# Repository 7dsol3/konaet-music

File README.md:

# KONAET Music

**A connected workspace. Music, public research, voice and a checkout code of your own.**

[Open KONAET Music on GitHub Pages](https://7dsol3.github.io/konaet-music/) ·
[Open the Sound Lab](https://7dsol3.github.io/konaet-music/sound-lab/) ·
[Audio methods](docs/SOUND-LAB.md) · [Digital hardware](docs/AUDIO-HARDWARE.md)

The GitHub Pages edition runs the catalog, comparison, bag, local music assistant,
checkout quotes, three QR artworks, test credits, logic lab and Sound Lab in the
visitor's browser. It does not depend on the author's PC or a temporary tunnel.
QR links carry a compact item selection and expiry; another device recomputes
the amount from the same bundled catalog. Quotes and receipts in this edition
are **unsigned browser demonstrations**, not bank requests or server-sealed records.
Public research calls selected external APIs and depends on network access.
No private customer/order fixtures or neural model keys are bundled.

Download the source and double-click **Run Browser Demo.cmd** on Windows, or run
`python scripts/serve_browser.py` on any supported PC. Python 3.11+ is required;
this browser launcher needs no pip packages. See [browser delivery](docs/GITHUB-PAGES.md).
The full Python edition remains available for server sessions, private fixture
order verification, sealed sandbox receipts and an optional local model.

This is the **separate product evolution** of the submitted
[Empório da Música technical case](https://github.com/7dsol3/emporio-musica-ai-agent).
The original submission is preserved at revision
`aefc6f54191eb00c52d7a9f8df85c1c3a201c5b6`. Its history is retained here;
new work belongs to this repository. [Scope and decisions](docs/EVOLUTION.md).

The customer interface and replies are in **English**. Catalog prices remain
in **BRL**. The store, inventory and customer fixtures are fictional supplied
case data. No real purchase, stock reservation, refund or charge is executed.

## Explore the product

**[Explore the H-01A KiCad project](hardware/h01-audio/README.md)** — editable
schematic, routed PCB, STEP/GLB, BOM and review Gerbers. Zero ERC/DRC/parity
violations; external FPGA required, physical bring-up not performed.

*Exported integer reference trace. Live analysis is in the Sound Lab; this animation
is not physical-device telemetry.*

- Browse 65 recorded instruments by category, brand, model, availability and budget.
- Compare two or three instruments using recorded specifications.
- Open a product, add it to a session bag and change quantities.
- Prepare a server-calculated, fifteen-minute checkout preview with a unique KONAET Code.
- Download the original vector code or open the quote on another device when deployed on HTTPS.
- Ask KONAET about instruments, prices, installments, store policies and a verified fixture order.
- Use the native Portuguese or English interface; voice drafts and spoken replies follow that language and remain opt-in.
- Install the responsive PWA on supported devices. Every command also works by typing.
- Choose Prisma or original liquid glass, with color, transparency, blur, corners, refractive light and comfort controls. The look is shared with Sound Lab and can be exported or imported.
- Research public knowledge, scholarly metadata and code with dated source links.
- Switch the voice/text assistant between the music desk and explicit research scopes.
- Inspect actual connection states and export source briefs from the current tab.
- Try a private test wallet, approve/decline a sandbox transaction and verify its sealed receipt.
- Export a private opening compatible with the Sovereign receipt SDK, without submitting to a network.
- Explore a Python/SystemVerilog credit gate and its logical trace in the hardware lab.
- Play named notes, build triads, use a metronome and export a project-authored four-chord study.
- Tune a sustained note with explicit microphone permission; analyze a local audio file without uploading it.
- Ask checked music rules to explain a pitch/triad estimate, with an optional, clearly named model suggestion.
- Generate phase controls for the H-01 digital audio core, hear its reference voice and inspect exact PCM metrics.

The **2.2 Sound Lab** is a separate, lazy page at `/sound-lab`. Its browser DSP is
project code, not a trained song-recognition model. H-01 includes synthesizable
SystemVerilog for three phase voices, exact level/energy meters and I²S transmit
and receive paths. The live site executes the reference model; no physical FPGA,
microphone board or DAC is connected to the server.

[Methods and limits](docs/SOUND-LAB.md) · [Hardware interfaces and equations](docs/AUDIO-HARDWARE.md) ·
[Production gates](docs/PRODUCTION-GATES.md) · [External-runtime comparison protocol](docs/RUNTIME-COMPARISON.md)

The listening room keeps its floating shell, tool rail, catalog search and
separate Discover, Research and Guide areas. Prisma supplies graphite materials,
physical controls and selected refractive edges; the original green glass room
remains selectable. Sound Lab shares the settings and typography. The supplied
six-board reference is mapped to actual functions in [Prisma Studio](docs/PRISMA-STUDIO.md).
The native PT/EN interface avoids browser translation altering the layout or
instrument identifiers. The browser assistant handles Portuguese instrument
families, Brazilian budget amounts and exact model lookups.

The room artwork is an original WebP of about 18 KB. Fonts are bundled under
their [Open Font Licenses](docs/FONT-PROVENANCE.md); there are no external font
requests or animation frameworks. Main text assets have a 280 KB raw / 86 KB
gzip budget, with separate 30 KB bitmap and 100 KB font budgets. Sound Lab's
audio engine stays lazy. Browser reviews cover PT/EN at seven widths, alongside
DOM and audio lifecycle tests. [Art direction and checks](docs/LISTENING-ROOM.md).

## Run locally

Python 3.11 or 3.12 is recommended. No paid key is required for the local mode.

```powershell
py -3.12 -m venv .venv
.\.venv\Scripts\python.exe -m pip install -r requirements-runtime.lock
.\.venv\Scripts\python.exe -m pip install --no-deps --no-build-isolation -e .
.\.venv\Scripts\python.exe -m emporio serve
```

Open **http://127.0.0.1:8000**. Alternatively, double-click **Run Offline.cmd**.
For the standalone browser edition instead, use **Run Browser Demo.cmd**; it
starts at **http://127.0.0.1:8040** and keeps working while that window is open.
The default agent uses explicit local rules and the same authoritative tools.
It is a deterministic router, not a neural language model.

For an actual local neural planner on Windows x64:

```powershell
.\.venv\Scripts\python.exe scripts/local_model.py setup
.\.venv\Scripts\python.exe scripts/local_model.py app
```

Or double-click **Run Demo.cmd**. Setup verifies approximately 665 MB of official
Qwen3-0.6B Q8_0 and llama.cpp assets before loading them. Qwen is an **external
inference model**, not weights trained by KONAET. Engine files are compared
against the pinned archive before execution. [Provenance](docs/PROVENANCE.md).

The terminal commands remain available:

```text
python -m emporio chat --language en
python -m emporio verify-audit
```

## KONAET Code

The illustration above is an actual scannable **source-link demonstration**.
It opens this repository. It is not a payment request or an active checkout.

Real application codes identify individual checkout previews. The backend
creates a cryptographically random reference, recalculates current prices,
checks quantities, applies eligible PIX pricing without stacking promotions,
and binds the result to an expiring immutable quote. Retrying the same request
for an unchanged bag returns the same quote. Changed contents require a new request.

The QR encoder is **Segno**, with high error correction and a four-module quiet
zone. KONAET's vector composition, brand, colors, framing and checkout binding
are implemented in [konaet_code.py](emporio/konaet_code.py). Branding does not
cover the finder patterns or data. No third-party QR image service receives
the checkout URL. An independent ZXing decoder tests the actual rendered SVG
at two widths and three orientations.

Choose **Signature**, **Orbit** or **Studio** artwork. Each keeps the exact same
quote URL and unobstructed symbol. The drawings sit outside the quiet zone.
The data itself has three source-generated treatments: horizontal circuit traces,
connected constellation dots and vertical studio ribbons. Finder, alignment,
timing, format and version modules retain their exact square geometry. No custom
scanner is required; compatibility is checked with an independent QR decoder.
The server uses a versioned unit-rounding rule consistently in bag and quote;
fractional-cent regression tests and every available catalog product are checked.

| Orbit / science | Studio / guitar |
| --- | --- |
|  |  |

These two documentation codes open the GitHub entrance. Active checkout codes
are generated separately for their unique expiring quote.

The link is a capability: anyone holding it can view its **public product
quote** until expiry. No email, customer ID, chat or session cookie is encoded.
Shipping is excluded. Stock is not reserved. The QR itself never proves payment.

For real commerce, the merchant needs an authorized store backend and payment
account. The researched next integration is a provider-issued Pix request with
idempotency and verified server-side confirmation. It is **not implemented or
enabled by a payment key in this release**. [Payment boundary and research](docs/PAYMENTS.md).

KONAET's new [sandbox checkout](docs/CHECKOUT-SANDBOX.md) is implemented separately:
test credits, typed intent creation, an atomic terminal outcome, exactly-once
debit on retries/concurrent confirmation, and server-sealed receipts. It does
not create a Pix payment, reserve stock or replace a regulated payment network.

## Voice and commands

Press the microphone in the assistant to request browser speech recognition.
Nothing listens on page load. The English transcript becomes an editable draft;
you choose when to send it. Enable **Read replies aloud** to use available
browser speech synthesis. Closing the assistant stops capture and playback.

Try:

```text
Show acoustic guitars under BRL 1,000
Tell me about the first one
Can I pay for it in 12 installments?
Compare the first two
Add the first one to my bag
Show my bag
Prepare checkout
```

The last commands are explicit UI actions over already displayed product IDs.
They cannot charge a card, submit a bank transfer or authorize a refund.

SpeechRecognition support varies. Some browsers send audio to their own speech
service; this is **not guaranteed offline speech**. Unsupported or denied
microphones keep typed chat available. Real microphone, mobile-device and
speech-quality testing is still required. [Voice contract](docs/VOICE.md).

## How the agent works

```mermaid
flowchart LR
  C[English text or reviewed voice draft] --> P[Local router or optional model planner]
  P --> G[Intent constraints and typed tool guards]
  G --> T[Catalog / policies / payment math / scoped order]
  T --> R[Grounded answer and source receipts]
  U[Explicit customer action] --> B[Session bag]
  B --> Q[Repriced expiring quote]
  Q --> K[KONAET Code]
```

Prices and policy outcomes come from checked tool results. Explicit category,
budget, product and transaction arguments cannot be widened by the model.
Order tools use session ownership in SQL. Private order requests bypass model
planning; provider context contains only allowlisted public product fields,
and order references are redacted from user history.

The local audit chain detects modification of existing receipts. It has no
external anchor and does not prevent an operator from replacing the entire
log. This product does not claim a Sovereign-finalized receipt or independent audit.

The inherited policy module remains version-pinned to the supplied PDF. Return
messages with missing packaging/materials now go to review rather than being
treated as fully satisfied. Ambiguous claims remain preliminary guidance.

## Configuration

| Variable | Purpose |
| --- | --- |
| `EMPORIO_PROVIDER` | `local` or `openai_compatible`; local is the default |
| `EMPORIO_MODEL_URL` | Native function-calling endpoint; HTTPS or HTTP loopback |
| `EMPORIO_MODEL` | Model ID accepted by your endpoint |
| `EMPORIO_MODEL_KEY` | Optional provider key, backend environment only |
| `EMPORIO_MODEL_TIMEOUT` | Planning timeout, 1–60 seconds |
| `EMPORIO_DATA_DIR` | Optional authorized replacement for the six original CSVs and manual |
| `EMPORIO_STATE_DIR` | Writable private state directory; defaults to the user's local state folder |
| `KONAET_PUBLIC_URL` | Trusted HTTPS origin used for checkout links; loopback is allowed for local use |
| `KONAET_MODEL_CACHE` | Optional directory holding verified neural-model assets |
| `KONAET_BRAVE_SEARCH_KEY` | Optional backend-only key for the general Web index; other documented public indexes work without it |
| `KONAET_GATEWAY_SECRET` | Preview-origin authentication, supplied only at runtime to the gateway and Python origin |

Variables are read from the process environment. `.env.example` is documentation,
not a file loader. A packaged wheel includes the case data and the web assets;
installation outside this checkout is tested.

## Host the Python application

The frontend and API must share an origin. Static GitHub Pages cannot execute
this Python/SQLite backend. A repository URL is not a hosted service.

An optional [Render demo blueprint](render.yaml) is included. It needs a Render
account, a connected copy of this repository and `KONAET_PUBLIC_URL` set to the
assigned HTTPS origin. It is not deployed automatically by cloning the code.
The free demo filesystem is ephemeral: sessions and quotes can disappear on
restart. Do not use it as a real merchant's order database.

For a Python host with an HTTPS reverse proxy:

```text
pip install -r requirements-runtime.lock
pip install --no-deps --no-build-isolation .
KONAET_PUBLIC_URL=https://your-demo.example PORT=8000 python scripts/serve.py
```

Set environment variables with your shell's syntax. The deployment entrypoint
requires the HTTPS origin, binds the assigned port and uses one process. A
production multi-instance service needs shared storage, verified customer
identity, independent rate limits, secrets management and monitoring.

## Verification

```text
python -m pip install -r requirements.lock
python -m pip install --no-deps --no-build-isolation -e .
python -m pytest
python scripts/verify_frontend.py
python scripts/verify_wheel.py
python scripts/capture_product_evidence.py
```

Interface event-contract tests run with Node 24.22.2:

```text
cd tests/ui
npm ci --ignore-scripts
cd ../..
node --test tests/ui/interface.test.mjs
```

These execute DOM events with API doubles. They do not render pixels or prove
physical microphone behavior. The native/browser-control bridge was unavailable
during implementation, so a new browser visual review is still outstanding.

See [2.1 validation and exact evidence](docs/VALIDATION-2.1.md) for the measured scope,
fresh model conversations, package tests and known limits. Historical screenshots
and `docs/ui-check.json` came from the original case and do not depict this redesign.

## Licensing and next work

Project-authored contributions use MIT. The frozen retrieval module retains
the Konaet Research and Commercial License, and the supplied case fixtures
retain their separate terms. The MIT license does not relicense those materials.
[Full notices](THIRD_PARTY_NOTICES.md). Qwen, llama.cpp, Segno and other dependencies
remain attributed to their authors.

OpenAI Codex assisted implementation, research, tests and documentation. The
project records observed failures and uses deterministic guardrails around
optional model planning. No claim of consciousness, general superiority,
original QR encoding, or outperforming Siri/Alexa is made.

Next: real browser/device accessibility and voice trials; authorized live-store
adapters; a payment-provider sandbox; broader unseen paraphrase evaluation;
measured concurrent-load testing and a production identity/storage architecture.

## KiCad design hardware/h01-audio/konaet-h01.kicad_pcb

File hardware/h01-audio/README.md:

# KONAET H-01A — audio carrier

An editable **KiCad 10.0.8** project for the H-01 digital audio core. This revision
connects an **external FPGA** to a stereo line DAC and an external I²S microphone
module. It supplies the 12.288 MHz reference clock and the carrier's 3.3 V rail.
It does not contain an FPGA, inference processor, Wi-Fi radio or trained AI model.

**Review prototype.** ERC, DRC, schematic/PCB parity and all 105 connected pad
assignments pass. There are no waived DRC violations or disconnected nets.
Those results verify the design files; the board has not been fabricated,
powered, acoustically measured or approved for manufacture. See
[validation.json](validation.json) for source hashes and [bring-up](BRING-UP.md).

## Open and inspect

1. Open [konaet-h01.kicad_pro](konaet-h01.kicad_pro) with KiCad 10.0.8 or newer.
2. Open PCB Editor and press **Alt+3** for KiCad's interactive 3D Viewer.
3. Rotate, zoom, inspect both sides and toggle component visibility.
4. Open the Schematic Editor to inspect the named nets and manufacturer pins.

The project includes its footprint library and STEP models with relative paths.
It does not need a global library installation to view this design.
Y1 deliberately uses a **3225 crystal-shaped geometric proxy**; its appearance
is not an Abracon-certified mechanical model. All other models are the frozen
KiCad library models listed in [LIBRARIES.md](LIBRARIES.md).

| Deliverable | File |
| --- | --- |
| Schematic, editable / PDF | [KiCad schematic](konaet-h01.kicad_sch) · [PDF](schematic.pdf) |
| Routed PCB, editable / layer PDF | [PCB](konaet-h01.kicad_pcb) · [PDF](layout.pdf) |
| CAD assembly | [STEP](konaet-h01.step) · [GLB](konaet-h01.glb) |
| Rendered views | [Top](board-top.png) · [Bottom](board-bottom.png) |
| Parts and assembly | [BOM](bom.csv) · [Placement](placement.csv) |
| Review fabrication outputs | [Gerbers and drill files](fabrication) |
| Electrical specification | [Circuit manifest](circuit.json) · [Netlist](netlist.xml) |
| Check results | [ERC](erc.json) · [DRC + parity](drc.json) · [Export hashes](exports.json) |

## Electrical contract

85 × 65 mm, 1.6 mm nominal FR-4, two copper layers, four 3.2 mm mounting holes.
38 placements include four mounting holes; 34 placements have 3D models.
Minimum trace/clearance 0.20 mm, ground pours on both layers. Final stack-up,
manufacturing tolerances and solder-mask rules need the chosen fabricator's review.

* **J1:** pin 1 regulated +5 V input, pin 2 ground. Use 4.75–5.25 V and an external
  current-limited supply; no USB-PD negotiation, mains input or battery charger.
  SS14 provides series reverse-polarity protection. U1 is TLV75533PDBVR.
* **J2:** custom 2×6 header, **not PMOD**. Odd pins 1/3/5/7/9/11 are MCLK out,
  BCLK in, LRCLK in, DAC data in, microphone data out and DAC_UNMUTE in.
  Every even pin is ground. No supply rail is connected to J2. The FPGA is
  separately powered, uses 3.3 V I/O, and must share ground. Keep the cable short;
  source termination and signal integrity must be verified on the actual host.
* **J3:** 1=3.3 V output, 2=ground, 3=BCLK, 4=LRCLK, 5=mic serial data, 6=ground
  for a module's LR select. External I²S module only, not an analog or PDM mic.
  Budget ≤10 mA for the module. The host captures the left channel and the first
  16 significant bits of a 32-bit slot. A 24-bit I²S source loses its low 8 bits.
  Do not treat this header as a drop-in socket for every microphone board.
* **J4:** 1=left line output, 2=ground, 3=right line output. Use a line input with
  **≥10 kΩ** impedance. This is not a headphone or loudspeaker amplifier.

U2 PCM5102APWR uses 3-wire I²S, with SCK grounded and its BCLK PLL active.
FMT=0 selects I²S, FLT=0 normal latency, DEMP=0 de-emphasis off. XSMT has a
100 kΩ pull-down: output remains muted until the host explicitly drives J2.11 high.
Each line output has 470 Ω + 2.2 nF filtering (nominal RC corner ≈154 kHz).
The supply and charge-pump capacitors follow the manufacturer's application values.
The shared ground is intentional; this is not an isolated audio interface.

At 48 kHz: MCLK=256fs=12.288 MHz, BCLK=64fs=3.072 MHz. The existing
[SystemVerilog core](../../emporio/gateware/konaet_audio_core.sv) provides serial
TX/RX, three oscillator voices and peak/energy meters. A selected FPGA still
needs its own pin constraints, reset/unmute sequencing and host control bridge.
The website's synthesis/analysis is a software reference; opening the site does
not program or connect this board.

## Calculations and limits

The carrier budget is **100 mA maximum on the 3.3 V rail**, including a ≤10 mA
external mic module. It is a design allocation, not a measured current. At an
assumed 4.6 V LDO input, dissipation is `(4.6−3.3) × 0.1 = 0.13 W`; actual diode
drop, thermal rise, copper spreading and startup current require bench checks.
No 500 mA system capability is inferred from the regulator's headline rating.

The three-voice core is bounded to 12,288/32,768 full scale. The DAC's specified
full-scale line level is not a measurement of this board. Jitter, distortion,
noise, crosstalk and frequency response are **unmeasured**. Auto-routed traces were
checked geometrically; analog return paths and decoupling effectiveness need
engineering review before ordering. Unplanned power loss can still produce pops.

## Reproduce checks and exports

Using KiCad's bundled Python (or Linux Python with `pcbnew`):

```sh
python scripts/hardware/verify_h01.py --cli kicad-cli
python scripts/hardware/export_h01.py --cli kicad-cli
```

The validator runs real ERC and DRC with schematic parity, rejects all errors
and warnings, compares the schematic and PCB pads to `circuit.json`, checks
local 3D paths, geometry and source hashes. CI uses a pinned official KiCad image.
Exports are regenerated only after current source hashes pass.

To regenerate placement from code, `build_h01.py --library <KiCad share/kicad>`
**replaces the PCB with an unrouted placement**. Route its DSN with Freerouting
2.5.0, then `finish_h01.py --session <file.ses>`, `sync_h01_fields.py`, and validate.
The checked-in routed PCB is the reviewed result; routing is not asserted bitwise
deterministic. Do not run the placement generator over manual edits without a branch.

## Primary design references

* [TI PCM5102A, SLAS859C](https://www.ti.com/lit/ds/symlink/pcm5102a.pdf): pinout,
  hardware configuration, charge pump, filters and power sequencing.
* [TI TLV755P, SBVS320D](https://www.ti.com/lit/ds/symlink/tlv755p.pdf): DBV pinout,
  rail limits and capacitor requirements.
* [Abracon ASE series](https://abracon.com/Oscillators/ASEseries.pdf): 3.3 V
  oscillator, enable, output and package.
* [NXP I²S specification](https://www.nxp.com/docs/en/user-manual/UM11732.pdf):
  serial timing contract.

The design is original project integration of standard circuits, not a claim to
have invented I²S, these ICs or a processor superior to Siri/Alexa hardware.

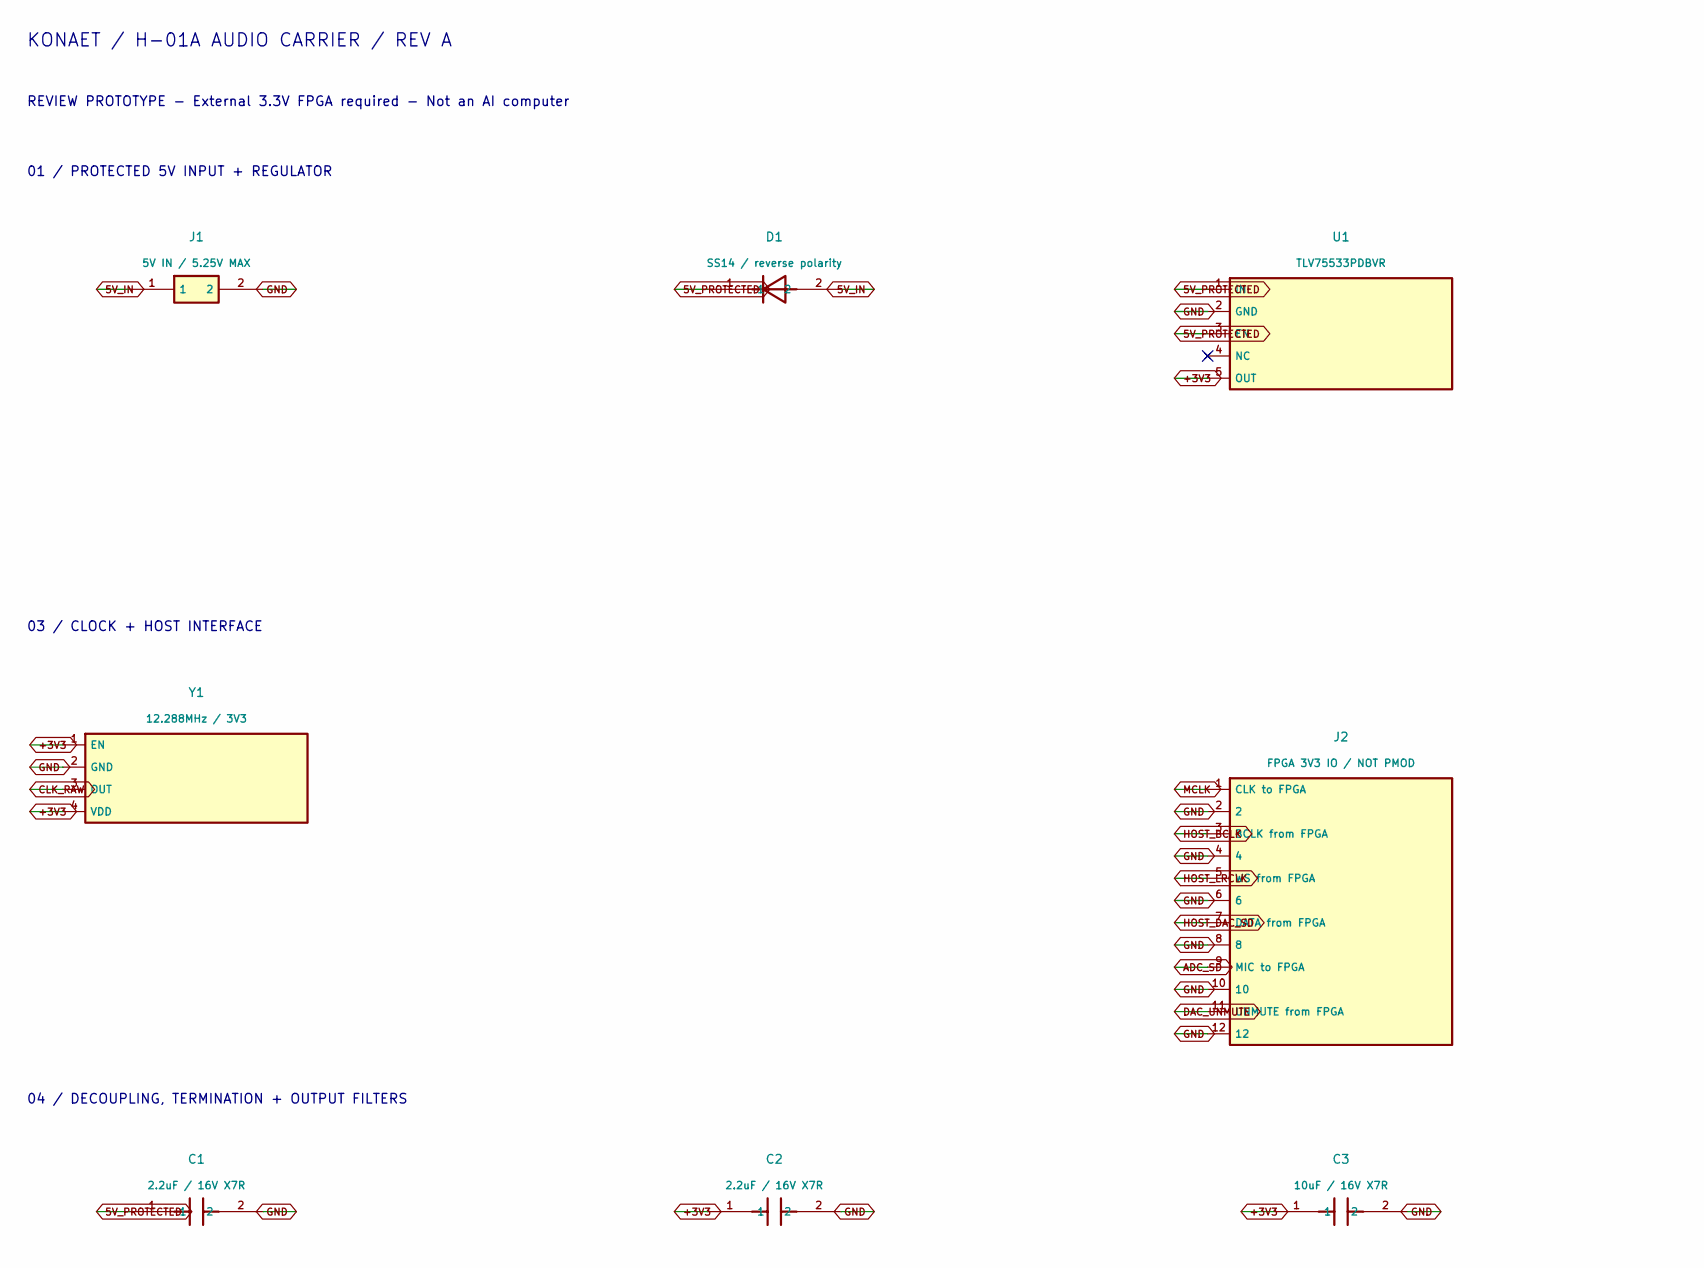
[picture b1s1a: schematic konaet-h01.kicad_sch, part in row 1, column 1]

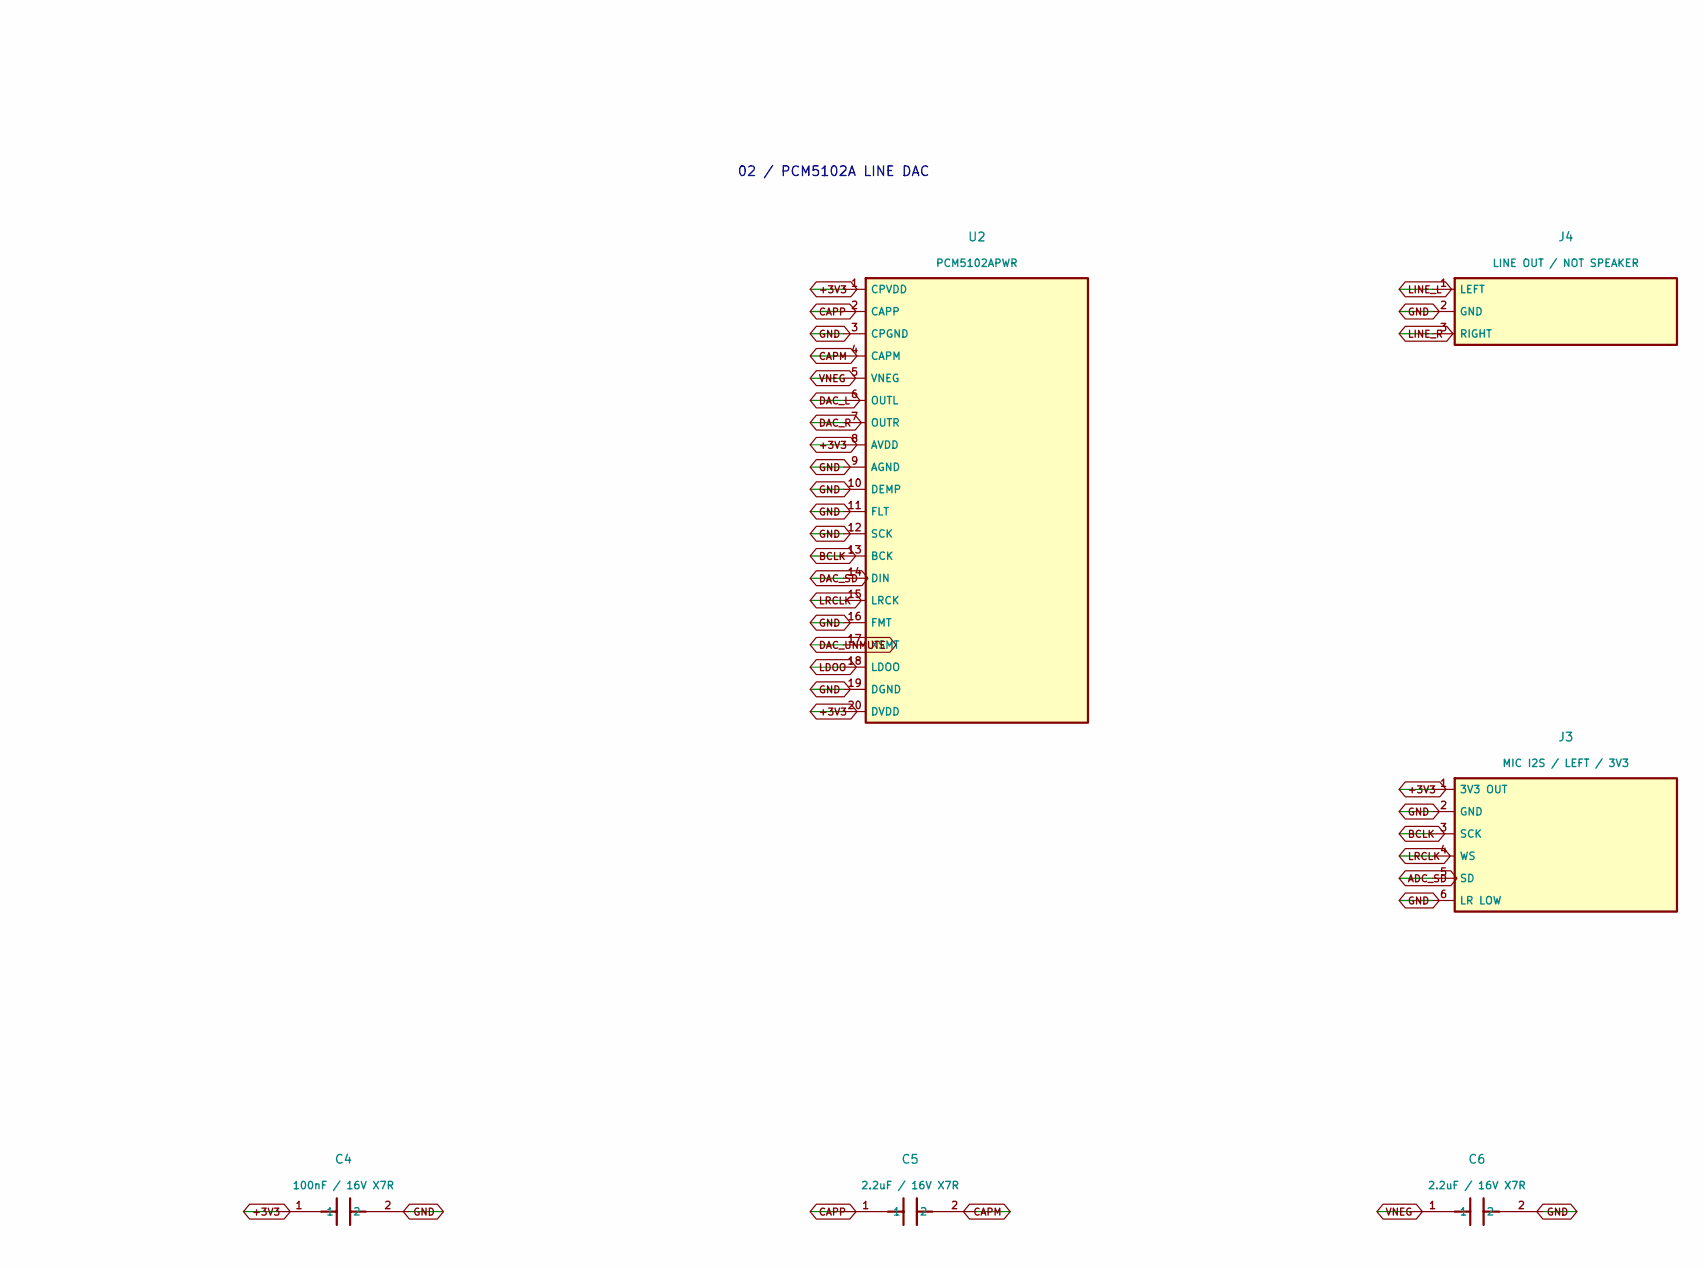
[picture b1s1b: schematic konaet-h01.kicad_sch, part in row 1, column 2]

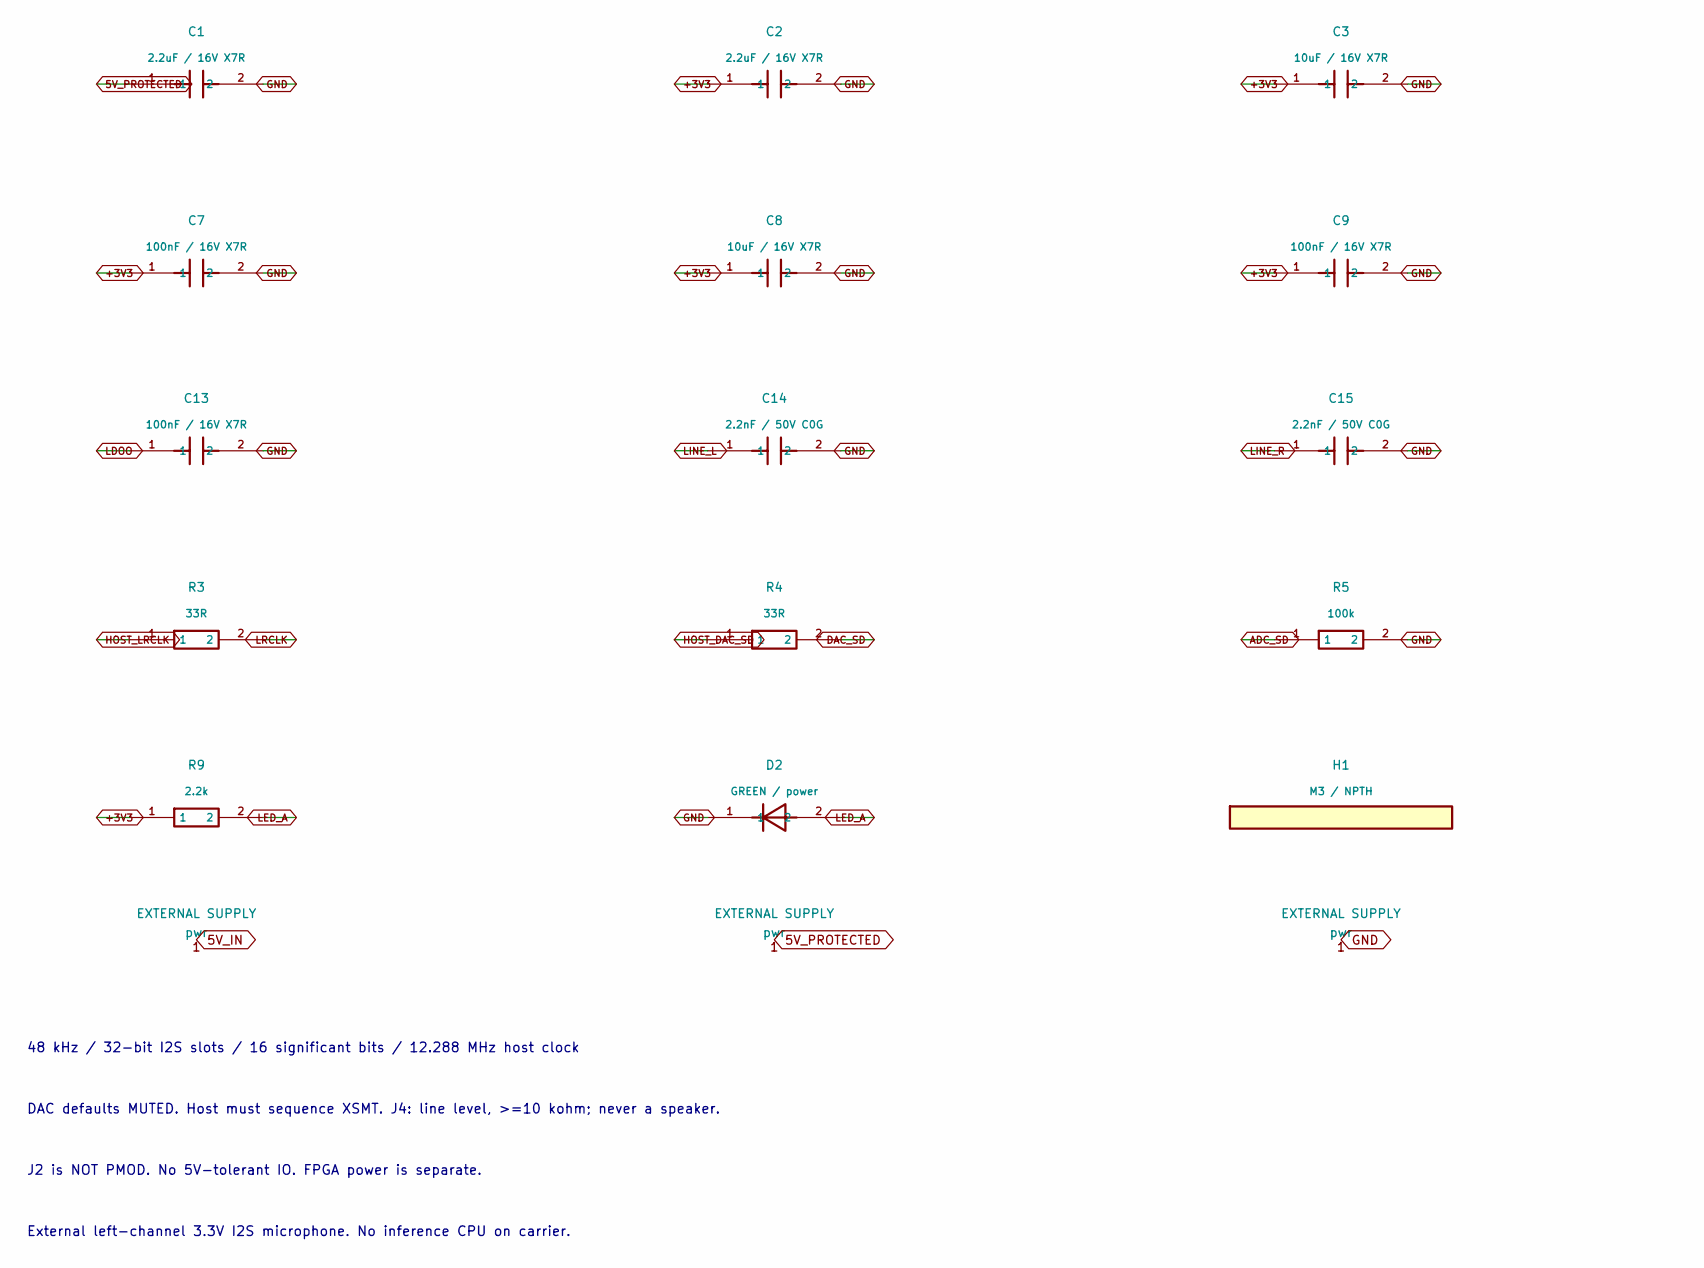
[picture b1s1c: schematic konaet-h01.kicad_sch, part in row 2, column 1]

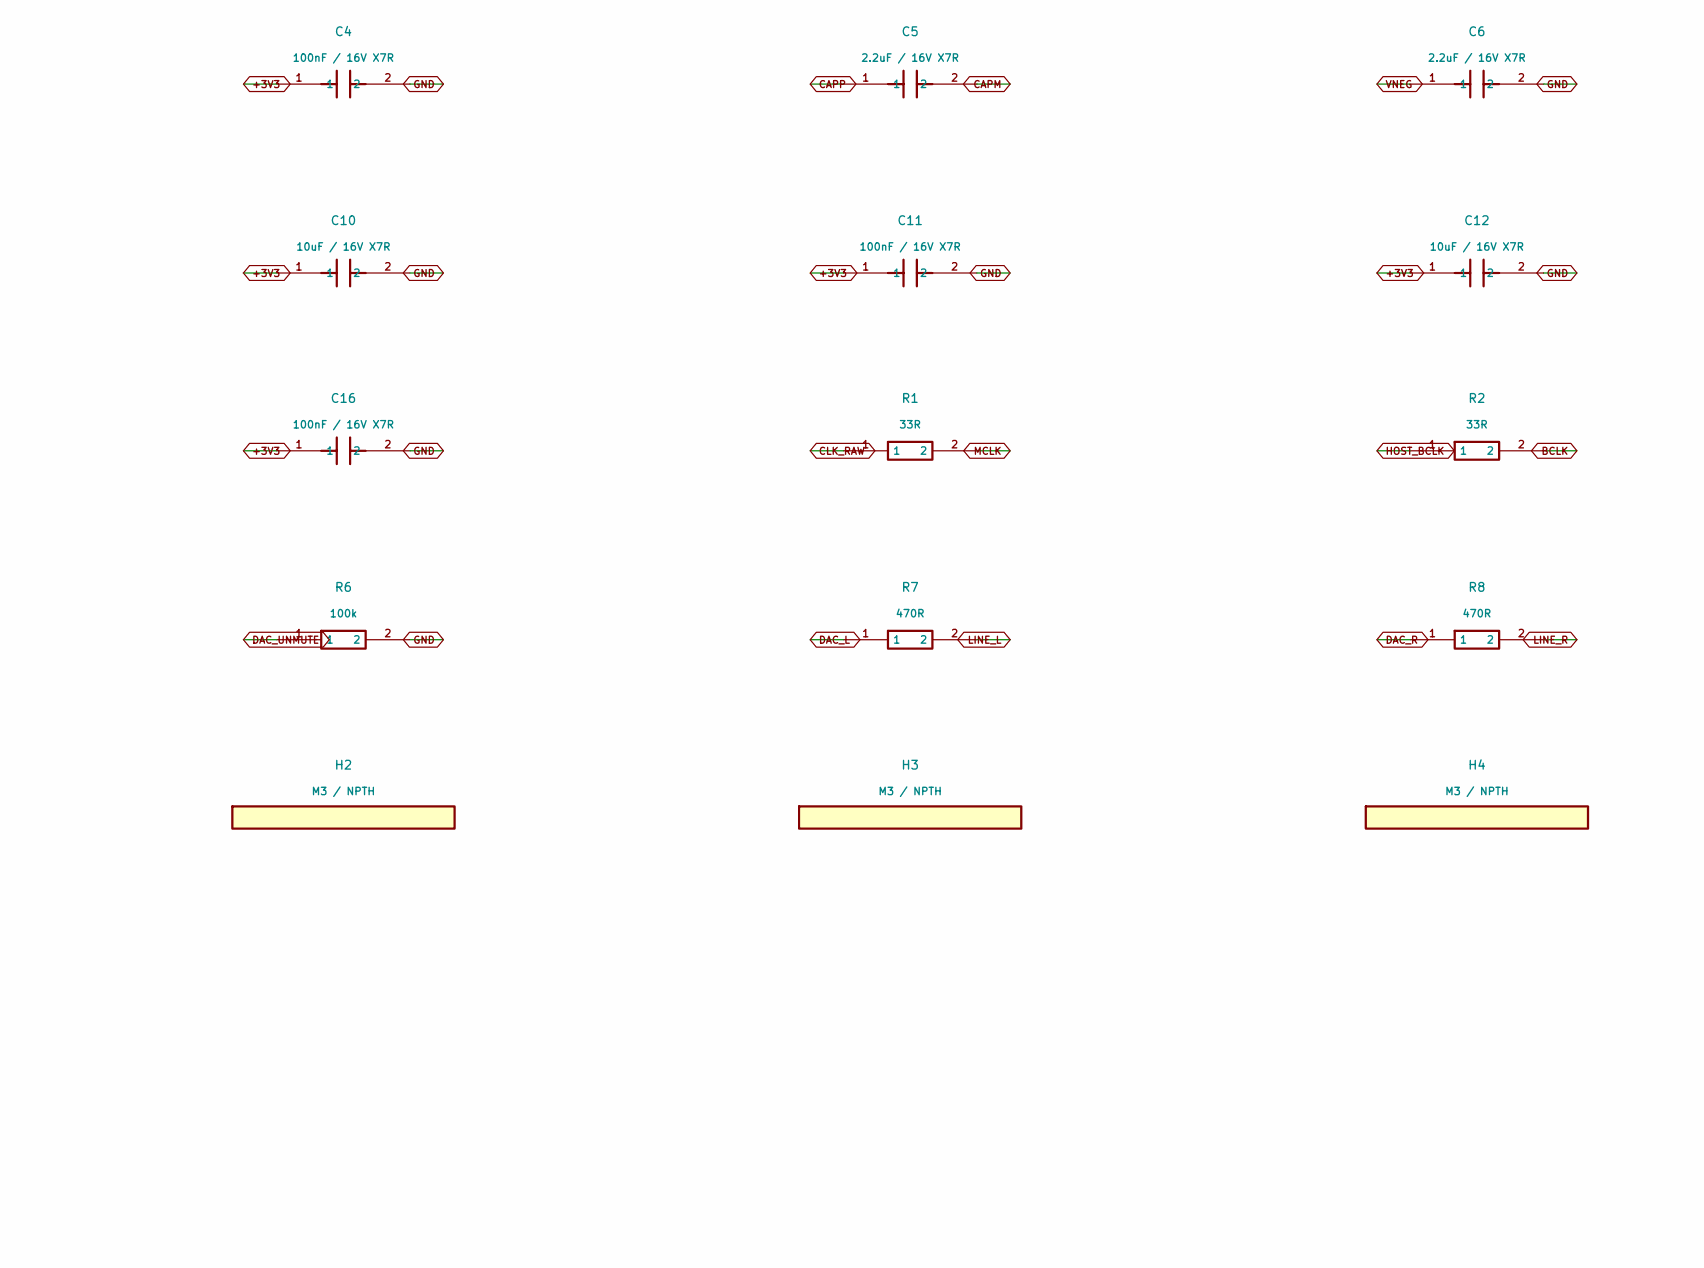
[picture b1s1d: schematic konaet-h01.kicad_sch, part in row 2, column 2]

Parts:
C1: 2.2uF / 16V X7R; C1; MPN 2.2uF / 16V X7R
C2: 2.2uF / 16V X7R; C2; MPN 2.2uF / 16V X7R
C3: 10uF / 16V X7R; C3; MPN 10uF / 16V X7R
C4: 100nF / 16V X7R; C4; MPN 100nF / 16V X7R
C5: 2.2uF / 16V X7R; C5; MPN 2.2uF / 16V X7R
C6: 2.2uF / 16V X7R; C6; MPN 2.2uF / 16V X7R
C7: 100nF / 16V X7R; C7; MPN 100nF / 16V X7R
C8: 10uF / 16V X7R; C8; MPN 10uF / 16V X7R
C9: 100nF / 16V X7R; C9; MPN 100nF / 16V X7R
C10: 10uF / 16V X7R; C10; MPN 10uF / 16V X7R
C11: 100nF / 16V X7R; C11; MPN 100nF / 16V X7R
C12: 10uF / 16V X7R; C12; MPN 10uF / 16V X7R
C13: 100nF / 16V X7R; C13; MPN 100nF / 16V X7R
C14: 2.2nF / 50V C0G; C14; MPN 2.2nF / 50V C0G
C15: 2.2nF / 50V C0G; C15; MPN 2.2nF / 50V C0G
C16: 100nF / 16V X7R; C16; MPN 100nF / 16V X7R
D1: SS14 / reverse polarity; D1; MPN SS14
D2: GREEN / power; D2; MPN 0805 green LED
H1: M3 / NPTH; H1; MPN M3 / NPTH
H2: M3 / NPTH; H2; MPN M3 / NPTH
H3: M3 / NPTH; H3; MPN M3 / NPTH
H4: M3 / NPTH; H4; MPN M3 / NPTH
J1: 5V IN / 5.25V MAX; J1; MPN B2B-XH-A(LF)(SN)
J2: FPGA 3V3 IO / NOT PMOD; J2; MPN 2x6 2.54mm header
J3: MIC I2S / LEFT / 3V3; J3; MPN 1x6 2.54mm header
J4: LINE OUT / NOT SPEAKER; J4; MPN 1x3 2.54mm header
R1: 33R; R1; MPN 33R
R2: 33R; R2; MPN 33R
R3: 33R; R3; MPN 33R
R4: 33R; R4; MPN 33R
R5: 100k; R5; MPN 100k
R6: 100k; R6; MPN 100k
R7: 470R; R7; MPN 470R
R8: 470R; R8; MPN 470R
R9: 2.2k; R9; MPN 2.2k
U1: TLV75533PDBVR; U1; MPN TLV75533PDBVR
U2: PCM5102APWR; U2; MPN PCM5102APWR
Y1: 12.288MHz / 3V3; Y1; MPN ASE-12.288MHZ-L-C-T

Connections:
5V_IN: D1.2, J1.1
5V_PROTECTED: C1.1, D1.1, U1.1 (IN), U1.3 (EN)
+3V3: C2.1, C3.1, C4.1, C7.1, C8.1, C9.1, C10.1, C11.1, C12.1, C16.1, J3.1 (3V3 OUT), R9.1, U1.5 (OUT), U2.1 (CPVDD), U2.8 (AVDD), U2.20 (DVDD), Y1.1 (EN), Y1.4 (VDD)
ADC_SD: J2.9 (MIC to FPGA), J3.5 (SD), R5.1
BCLK: J3.3 (SCK), R2.2, U2.13 (BCK)
CAPM: C5.2, U2.4 (CAPM)
CAPP: C5.1, U2.2 (CAPP)
CLK_RAW: R1.1, Y1.3 (OUT)
DAC_L: R7.1, U2.6 (OUTL)
DAC_R: R8.1, U2.7 (OUTR)
DAC_SD: R4.2, U2.14 (DIN)
DAC_UNMUTE: J2.11 (UNMUTE from FPGA), R6.1, U2.17 (XSMT)
GND: C1.2, C2.2, C3.2, C4.2, C6.2, C7.2, C8.2, C9.2, C10.2, C11.2, C12.2, C13.2, C14.2, C15.2, C16.2, D2.1, J1.2, J2.2, J2.4, J2.6, J2.8, J2.10, J2.12, J3.2 (GND), J3.6 (LR LOW), J4.2 (GND), R5.2, R6.2, U1.2 (GND), U2.3 (CPGND), U2.9 (AGND), U2.10 (DEMP), U2.11 (FLT), U2.12 (SCK), U2.16 (FMT), U2.19 (DGND), Y1.2 (GND)
HOST_BCLK: J2.3 (BCLK from FPGA), R2.1
HOST_DAC_SD: J2.7 (DATA from FPGA), R4.1
HOST_LRCLK: J2.5 (WS from FPGA), R3.1
LDOO: C13.1, U2.18 (LDOO)
LED_A: D2.2, R9.2
LINE_L: C14.1, J4.1 (LEFT), R7.2
LINE_R: C15.1, J4.3 (RIGHT), R8.2
LRCLK: J3.4 (WS), R3.2, U2.15 (LRCK)
MCLK: J2.1 (CLK to FPGA), R1.2
VNEG: C6.1, U2.5 (VNEG)

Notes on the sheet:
KONAET / H-01A AUDIO CARRIER / REV A
REVIEW PROTOTYPE - External 3.3V FPGA required - Not an AI computer
01 / PROTECTED 5V INPUT + REGULATOR
02 / PCM5102A LINE DAC
03 / CLOCK + HOST INTERFACE
04 / DECOUPLING, TERMINATION + OUTPUT FILTERS
48 kHz / 32-bit I2S slots / 16 significant bits / 12.288 MHz host clock
DAC defaults MUTED. Host must sequence XSMT. J4: line level, >=10 kohm; never a speaker.
J2 is NOT PMOD. No 5V-tolerant IO. FPGA power is separate.
External left-channel 3.3V I2S microphone. No inference CPU on carrier.

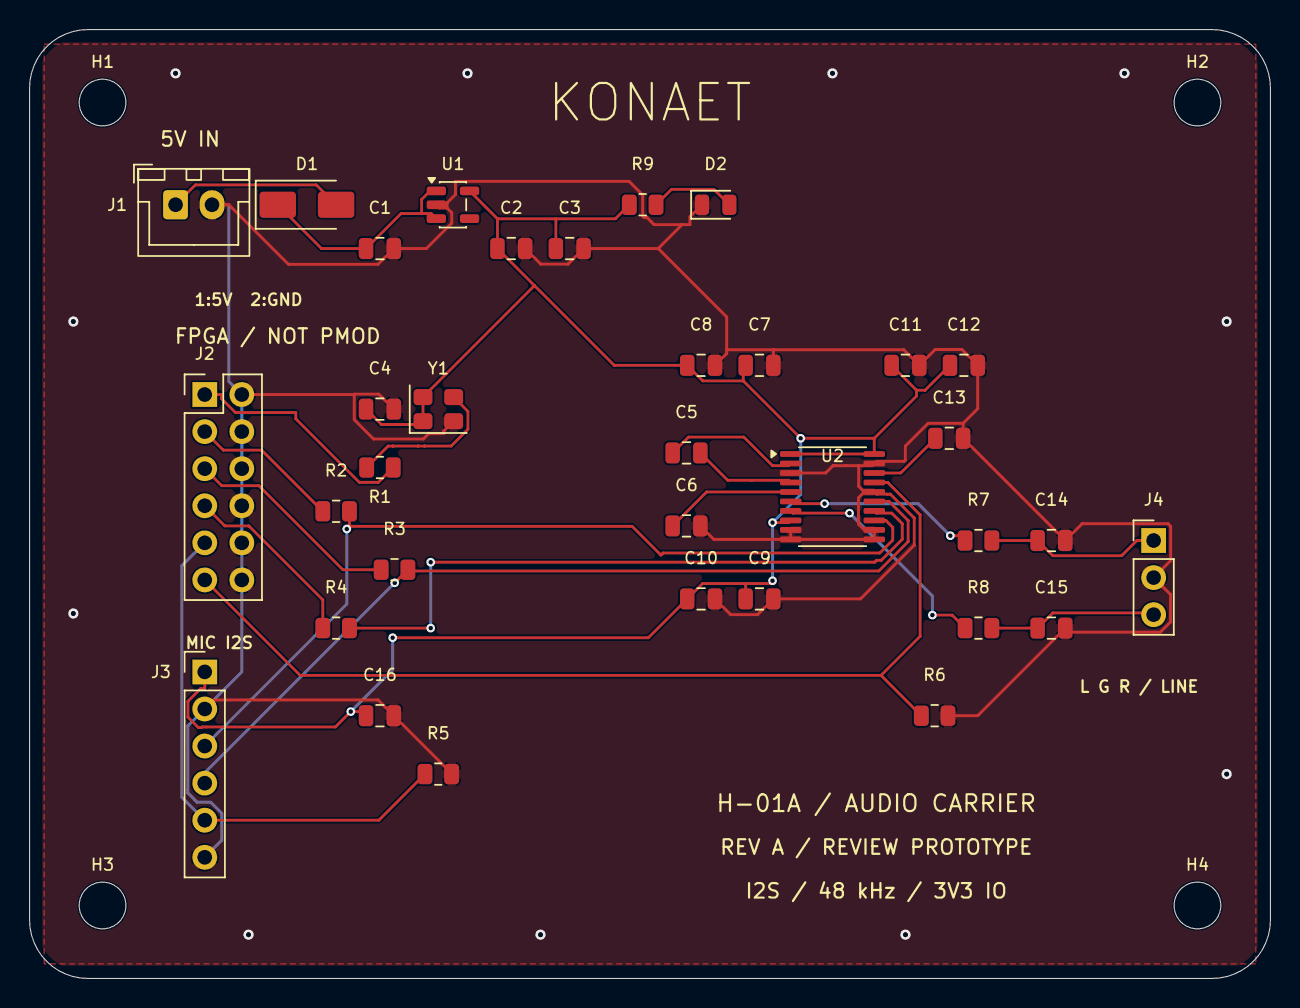
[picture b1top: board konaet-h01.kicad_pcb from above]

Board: 2 copper layers, 85.0 x 65.0 mm, 38 parts (0 on the bottom side), 23 nets.

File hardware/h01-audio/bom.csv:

Reference,Value,MPN_or_specification,KiCad_footprint,Datasheet
J1,5V IN / 5.25V MAX,B2B-XH-A(LF)(SN),Connector_JST:JST_XH_B2B-XH-A_1x02_P2.50mm_Vertical,https://www.jst-mfg.com/product/pdf/eng/eXH.pdf
D1,SS14 / reverse polarity,SS14,Diode_SMD:D_SMA,https://www.vishay.com/docs/88746/ss12.pdf
U1,TLV75533PDBVR,TLV75533PDBVR,Package_TO_SOT_SMD:SOT-23-5,https://www.ti.com/lit/ds/symlink/tlv755p.pdf
C1,2.2uF / 16V X7R,2.2uF / 16V X7R,Capacitor_SMD:C_0805_2012Metric,
C2,2.2uF / 16V X7R,2.2uF / 16V X7R,Capacitor_SMD:C_0805_2012Metric,
C3,10uF / 16V X7R,10uF / 16V X7R,Capacitor_SMD:C_0805_2012Metric,
C4,100nF / 16V X7R,100nF / 16V X7R,Capacitor_SMD:C_0805_2012Metric,
C5,2.2uF / 16V X7R,2.2uF / 16V X7R,Capacitor_SMD:C_0805_2012Metric,
C6,2.2uF / 16V X7R,2.2uF / 16V X7R,Capacitor_SMD:C_0805_2012Metric,
C7,100nF / 16V X7R,100nF / 16V X7R,Capacitor_SMD:C_0805_2012Metric,
C8,10uF / 16V X7R,10uF / 16V X7R,Capacitor_SMD:C_0805_2012Metric,
C9,100nF / 16V X7R,100nF / 16V X7R,Capacitor_SMD:C_0805_2012Metric,
C10,10uF / 16V X7R,10uF / 16V X7R,Capacitor_SMD:C_0805_2012Metric,
C11,100nF / 16V X7R,100nF / 16V X7R,Capacitor_SMD:C_0805_2012Metric,
C12,10uF / 16V X7R,10uF / 16V X7R,Capacitor_SMD:C_0805_2012Metric,
C13,100nF / 16V X7R,100nF / 16V X7R,Capacitor_SMD:C_0805_2012Metric,
C14,2.2nF / 50V C0G,2.2nF / 50V C0G,Capacitor_SMD:C_0805_2012Metric,
C15,2.2nF / 50V C0G,2.2nF / 50V C0G,Capacitor_SMD:C_0805_2012Metric,
C16,100nF / 16V X7R,100nF / 16V X7R,Capacitor_SMD:C_0805_2012Metric,
Y1,12.288MHz / 3V3,ASE-12.288MHZ-L-C-T,Oscillator:Oscillator_SMD_Abracon_ASE-4Pin_3.2x2.5mm,https://abracon.com/Oscillators/ASEseries.pdf
U2,PCM5102APWR,PCM5102APWR,Package_SO:TSSOP-20_4.4x6.5mm_P0.65mm,https://www.ti.com/lit/ds/symlink/pcm5102a.pdf
J2,FPGA 3V3 IO / NOT PMOD,2x6 2.54mm header,Connector_PinHeader_2.54mm:PinHeader_2x06_P2.54mm_Vertical,
J3,MIC I2S / LEFT / 3V3,1x6 2.54mm header,Connector_PinHeader_2.54mm:PinHeader_1x06_P2.54mm_Vertical,
J4,LINE OUT / NOT SPEAKER,1x3 2.54mm header,Connector_PinHeader_2.54mm:PinHeader_1x03_P2.54mm_Vertical,
R1,33R,33R,Resistor_SMD:R_0805_2012Metric,
R2,33R,33R,Resistor_SMD:R_0805_2012Metric,
R3,33R,33R,Resistor_SMD:R_0805_2012Metric,
R4,33R,33R,Resistor_SMD:R_0805_2012Metric,
R5,100k,100k,Resistor_SMD:R_0805_2012Metric,
R6,100k,100k,Resistor_SMD:R_0805_2012Metric,
R7,470R,470R,Resistor_SMD:R_0805_2012Metric,
R8,470R,470R,Resistor_SMD:R_0805_2012Metric,
R9,2.2k,2.2k,Resistor_SMD:R_0805_2012Metric,
D2,GREEN / power,0805 green LED,LED_SMD:LED_0805_2012Metric,
H1,M3 / NPTH,M3 / NPTH,MountingHole:MountingHole_3.2mm_M3,
H2,M3 / NPTH,M3 / NPTH,MountingHole:MountingHole_3.2mm_M3,
H3,M3 / NPTH,M3 / NPTH,MountingHole:MountingHole_3.2mm_M3,
H4,M3 / NPTH,M3 / NPTH,MountingHole:MountingHole_3.2mm_M3,
